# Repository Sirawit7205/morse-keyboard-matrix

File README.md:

# Morse Keyboard (Matrix Version)
This is a Morse Code Keyboard that's built only with common logic ICs. 

**Note: While I'm trying to follow morse code standard, I did not guaranteed that it will conform to ham radio standards and regulations. Use at your own risk.**

## Features

- Outputs full english alphabets, numbers, and 12 control codes.
- Built-In Keyboard Encoder circuit, connects any keypad matrix to the board to get started.
- 512 characters FIFO buffer.
- Manual Switch
- External key connector.
- Output buzzer and relay.

## Licensing

Hardware is licensed under `SPDX-License-Identifier: Apache-2.0 WITH SHL-2.1`

Documentation is licensed under `SPDX-License-Identifier: CC-BY-SA-4.0`

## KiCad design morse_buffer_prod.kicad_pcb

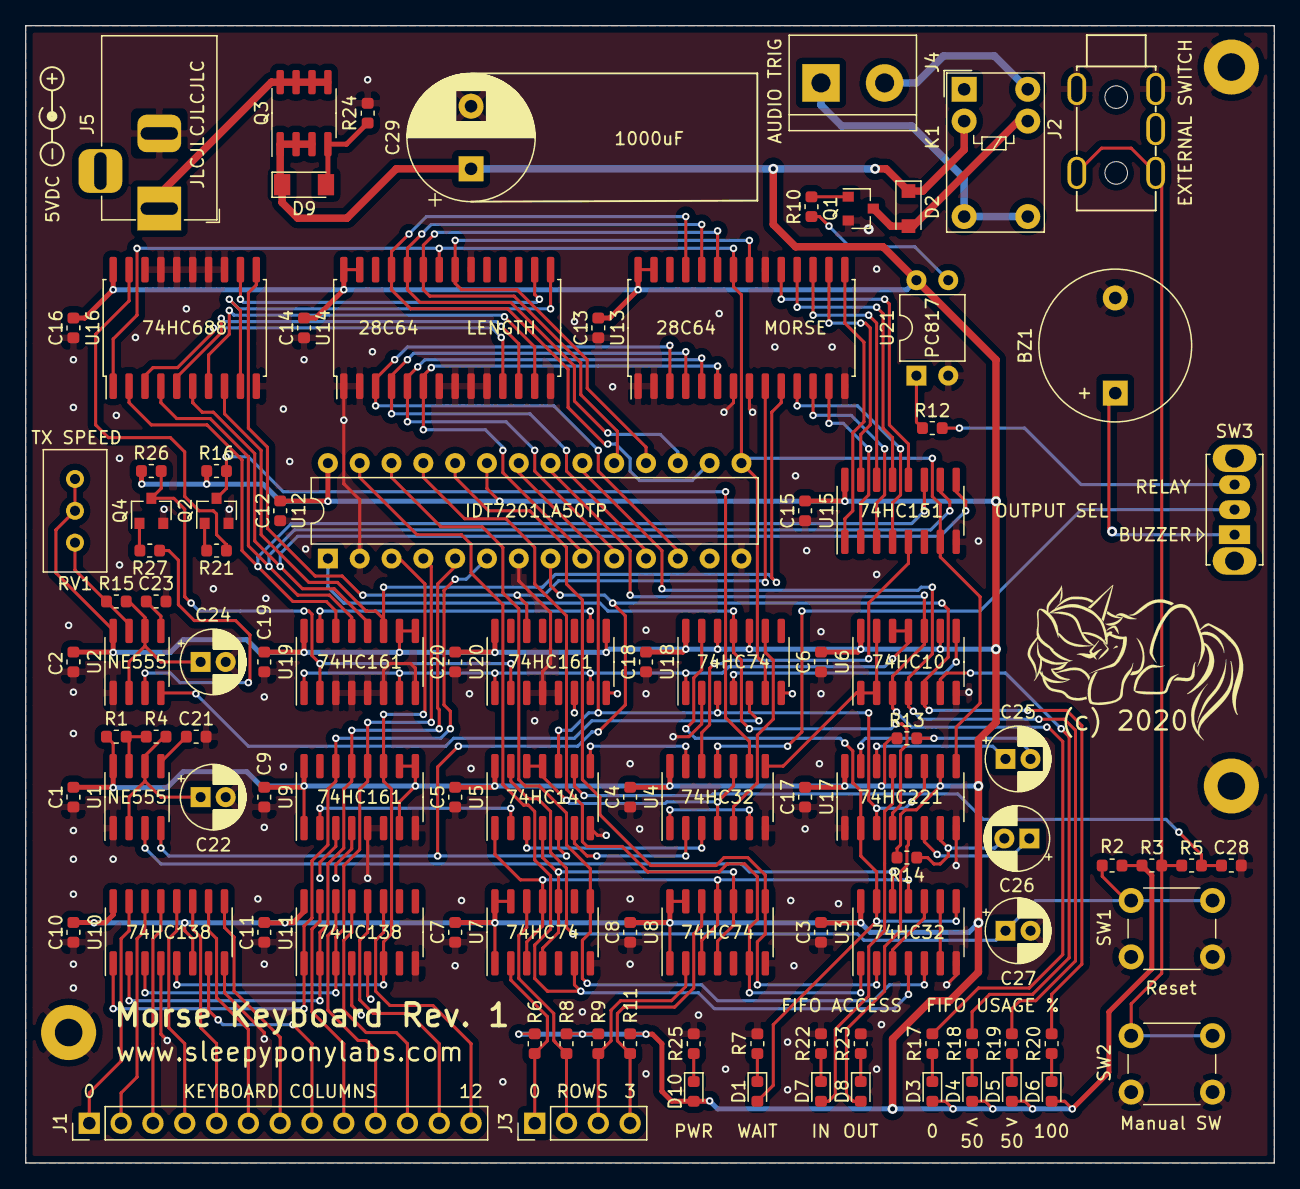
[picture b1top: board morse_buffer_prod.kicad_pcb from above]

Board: 2 copper layers, 99.7 x 90.8 mm, 105 parts (0 on the bottom side), 119 nets.

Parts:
BZ1: Buzzer; Buzzer_12x9.5RM7.6
C1, C2, C3, C4, C5, C6, C7, C8, C9, C10, C11, C12, C13, C14, C15, C16, C17, C18, C19, C20, C28: 100nF; C_0603_1608Metric
C21, C23: 10nF; C_0603_1608Metric
C22, C24, C25, C26, C27: 10uF; CP_Radial_D5.0mm_P2.00mm
C29: 1000uF; CP_Radial_D10.0mm_P5.00mm
D1: TX/WAIT; LED_0603_1608Metric
D2: 1N4007; D_SOD-123F
D3: ~EF; LED_0603_1608Metric
D4: RD; LED_0603_1608Metric
D5: ~HF; LED_0603_1608Metric
D6: ~FF; LED_0603_1608Metric
D7: IN_ACK; LED_0603_1608Metric
D8: OUT_ACK; LED_0603_1608Metric
D9: ZMM6V2; D_MiniMELF
D10: Power; LED_0603_1608Metric
H1, H2, H3: M2; MountingHole_2.2mm_M2_Pad
J1: Columns; PinHeader_1x13_P2.54mm_Vertical
J2: EXT_SW; PJ-313
J3: Rows; PinHeader_1x04_P2.54mm_Vertical
J4: TRIG_OUT; TerminalBlock_bornier-2_P5.08mm
J5: Barrel_Jack_Switch; BarrelJack_Horizontal
K1: G5V-1; Relay_SPDT_Omron_G5V-1
Q1, Q2, Q4: MMBT2222A; SOT-23
Q3: NCE30P12S; SOIC-8_3.9x4.9mm_P1.27mm
R1, R5: 470R; R_0603_1608Metric
R2, R6, R7, R8, R9, R11, R13, R14, R16, R17, R18, R19, R20, R21, R22, R23, R25, R26, R27: 4K7; R_0603_1608Metric
R3, R15: 10K; R_0603_1608Metric
R4, R10, R12: 1K; R_0603_1608Metric
R24: 100K; R_0603_1608Metric
RV1: 100k; Potentiometer_Bourns_3296W_Vertical
SW1: M_RST; SW_PUSH_6mm
SW2: BTN; SW_PUSH_6mm
SW3: OUTPUT_SEL; SW_Slide_1P2T_CK_OS102011MS2Q
U1, U2: NE555D; SOIC-8_3.9x4.9mm_P1.27mm
U3, U4: 74HC32; SOIC-14_3.9x8.7mm_P1.27mm
U5: 74HC14; SOIC-14_3.9x8.7mm_P1.27mm
U6: 74HC10; SOIC-14_3.9x8.7mm_P1.27mm
U7, U8, U18: 74HC74; SOIC-14_3.9x8.7mm_P1.27mm
U9, U19, U20: 74HC161; SOIC-16_3.9x9.9mm_P1.27mm
U10, U11: 74HC138; SOIC-16_3.9x9.9mm_P1.27mm
U12: IDT7201LA50TP; DIP-28_W7.62mm
U13: MORSE_EEPROM; SOIC-28W_7.5x17.9mm_P1.27mm
U14: LENGTH_EEPROM; SOIC-28W_7.5x17.9mm_P1.27mm
U15: 74HC151; SOIC-16_3.9x9.9mm_P1.27mm
U16: 74HC688; SOIC-20W_7.5x12.8mm_P1.27mm
U17: 74HC221; SOIC-16_3.9x9.9mm_P1.27mm
U21: PC817; DIP-4_W7.62mm

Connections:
+5V: C1.1, C2.1, C3.1, C4.1, C5.1, C6.1, C7.1, C8.1, C9.1, C10.1, C11.1, C12.1, C13.1, C14.1, C15.1, C16.1, C17.1, C18.1, C19.1, C20.1, C29.1, D2.1, D3.2, D4.2, D5.2, D6.2, D9.1, D10.2, K1.2, Q3.1, Q3.2, Q3.3, R1.1, R2.1, R3.1, R6.1, R8.1, R9.1, R11.1, R13.1, R14.1, R16.1, R26.1, RV1.1, RV1.2, U1.8, U2.8, U3.14, U4.14, U5.14, U6.9, U6.14, U7.1, U7.13, U7.14, U8.1, U8.13, U8.14, U9.1, U9.7, U9.9, U9.10, U9.16, U10.6, U10.16, U11.16, U12.23, U12.28, U13.27, U13.28, U14.27, U14.28, U15.16, U16.20, U17.10, U17.16, U18.10, U18.12, U18.14, U19.9, U19.10, U19.16, U20.9, U20.16, U21.4
/58Hz_Square: U1.3, U3.12
/CL0: U12.9, U13.6, U14.6
/CL1: U12.10, U13.5, U14.5
/CL2: U12.11, U13.4, U14.4
/CL3: U12.12, U13.3, U14.3
/LN0: U14.11, U16.3
/LN1: U14.12, U16.5
/LN2: U14.13, U16.7
/LN3: U14.15, U16.9
/LN4: U14.16, U16.12
/RW0: U12.16, U13.25, U14.25
/RW1: U12.17, U13.24, U14.24
/RW2: U12.18, U13.21, U14.21
/RW3: U12.19, U13.23, U14.23
/ST0: U15.11, U16.2, U19.14
/ST1: U15.10, U16.4, U19.13
/ST2: U15.9, U16.6, U19.12
/ST3: U13.10, U16.8, U19.11
/ST4: U13.9, U16.11, U20.14
BUZZER: BZ1.1, SW3.1
COL_0: U9.14, U10.1, U11.1, U12.6
COL_1: U9.13, U10.2, U11.2, U12.5
COL_2: U9.12, U10.3, U11.3, U12.4
COL_3: U9.11, U10.5, U11.6, U12.3
GNDREF: BZ1.2, C1.2, C2.2, C3.2, C4.2, C5.2, C6.2, C7.2, C8.2, C9.2, C10.2, C11.2, C12.2, C13.2, C14.2, C15.2, C16.2, C17.2, C18.2, C19.2, C20.2, C21.2, C22.2, C23.2, C24.2, C27.2, C28.2, C29.2, H1.1, H2.1, H3.1, J2.S, J5.2, Q1.2, Q2.2, Q4.2, R7.2, R22.2, R23.2, R24.2, R25.2, SW1.2, SW2.2, U1.1, U2.1, U3.7, U4.7, U5.7, U6.7, U7.7, U8.7, U9.3, U9.4, U9.5, U9.6, U9.8, U10.4, U10.8, U11.4, U11.5, U11.8, U12.2, U12.7, U12.14, U13.1, U13.2, U13.7, U13.8, U13.14, U13.20, U14.1, U14.2, U14.7, U14.8, U14.9, U14.10, U14.14, U14.20, U15.8, U16.10, U16.13, U16.14, U16.15, U16.16, U16.17, U16.18, U17.1, U17.8, U18.2, U18.7, U19.3, U19.4, U19.5, U19.6, U19.8, U20.3, U20.4, U20.5, U20.6, U20.8, U21.2
KEYBOARD_PRESS: D1.2, U3.8, U3.13, U17.2, U18.13
unnamed: C21.1, U1.5
unnamed: C22.1, R4.2, U1.2, U1.6
unnamed: C23.1, U2.5
unnamed: C24.1, R15.2, U2.2, U2.6
unnamed: C25.1, U17.14
unnamed: C25.2, R13.2, U17.15
unnamed: C26.1, U17.6
unnamed: C26.2, R14.2, U17.7
unnamed: C27.1, R2.2, SW1.1, U5.13
unnamed: C28.1, R5.1, U5.9
unnamed: D1.1, R7.1
unnamed: D2.2, K1.9, Q1.3
unnamed: D3.1, R17.1
unnamed: D4.1, R18.1
unnamed: D5.1, R19.1
unnamed: D6.1, R20.1
unnamed: D7.1, R22.1
unnamed: D7.2, U17.13
unnamed: D8.1, R23.1
unnamed: D8.2, U17.5
unnamed: D9.2, Q3.4, R24.1
unnamed: D10.1, R25.1
unnamed: J1.1, U10.15
unnamed: J1.2, U10.14
unnamed: J1.3, U10.13
unnamed: J1.4, U10.12
unnamed: J1.5, U10.11
unnamed: J1.6, U10.10
unnamed: J1.7, U10.9
unnamed: J1.8, U10.7
unnamed: J1.9, U11.15
unnamed: J1.10, U11.14
unnamed: J1.11, U11.13
unnamed: J1.12, U11.12
unnamed: J1.13, U11.11
unnamed: J2.T, R3.2, R5.2, SW2.1
unnamed: J3.1, R6.2, U7.2
unnamed: J3.2, R8.2, U7.12
unnamed: J3.3, R9.2, U8.2
unnamed: J3.4, R11.2, U8.12
unnamed: J4.1, K1.5, K1.6
unnamed: J4.2, K1.10
unnamed: J5.1, Q3.5, Q3.6, Q3.7, Q3.8
unnamed: Q1.1, R10.1
unnamed: Q2.1, R21.1
unnamed: Q4.1, R27.1
unnamed: Q4.3, R26.2, U19.2, U20.2
unnamed: R1.2, R4.1, U1.7
unnamed: R10.2, U21.3
unnamed: R12.1, U21.1
unnamed: R15.1, RV1.3, U2.7
unnamed: R18.2, U6.6
unnamed: R21.2, U16.19
unnamed: R27.2, U2.3
unnamed: SW3.2, U4.11
unnamed: U3.6, U3.9
unnamed: U3.3, U3.10
unnamed: U3.11, U5.1, U7.3, U7.11, U8.3, U8.11
unnamed: U4.2, U5.6
unnamed: U4.3, U5.3
unnamed: U4.4, U4.10, U5.11, U5.12
unnamed: U5.2, U9.2
unnamed: U5.4, U7.4, U7.10, U8.4, U8.10
unnamed: U13.11, U15.4
unnamed: U13.12, U15.3
unnamed: U13.13, U15.2
unnamed: U13.15, U15.1
unnamed: U13.16, U15.15
unnamed: U13.17, U15.14
unnamed: U13.18, U15.13
unnamed: U13.19, U15.12
unnamed: U6.8, U18.4
unnamed: U19.15, U20.10
RD_COMPLETE: U4.5, U18.9
RD_RESET: U4.1, U4.6
RELAY: R12.2, SW3.3
ROW_0: U3.4, U7.6, U12.27
ROW_1: U3.5, U7.8, U12.26
ROW_2: U3.1, U8.6, U12.25
ROW_3: U3.2, U8.8, U12.24
SOUND_TRIG_A: U4.12, U15.5
SOUND_TRIG_B: U4.13, U5.8
TX_COMPLETE: Q2.3, R16.2, U4.9
TX_ON: U2.4, U18.5
TX_RESET: U4.8, U6.1, U6.2, U6.13
~EMPTY: R17.2, U6.3, U6.10, U12.21
~FULL: R20.2, U1.4, U5.5, U6.5, U12.8
~HALF: R19.2, U6.4, U12.20
~PWRON_RESET: U5.10, U12.22, U17.3, U17.11, U18.3
~RX_ON: U12.1, U17.4, U18.11
~TX_ON: U12.15, U13.22, U14.22, U15.7, U16.1, U17.9, U18.6
~TX_RESET: U6.11, U6.12, U18.1, U19.1, U19.7, U20.1, U20.7

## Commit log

2021-01-03 Add gerber, sch, render, ibom, and license

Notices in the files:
morse_buffer_prod.kicad_pcb:
(c) 2020
